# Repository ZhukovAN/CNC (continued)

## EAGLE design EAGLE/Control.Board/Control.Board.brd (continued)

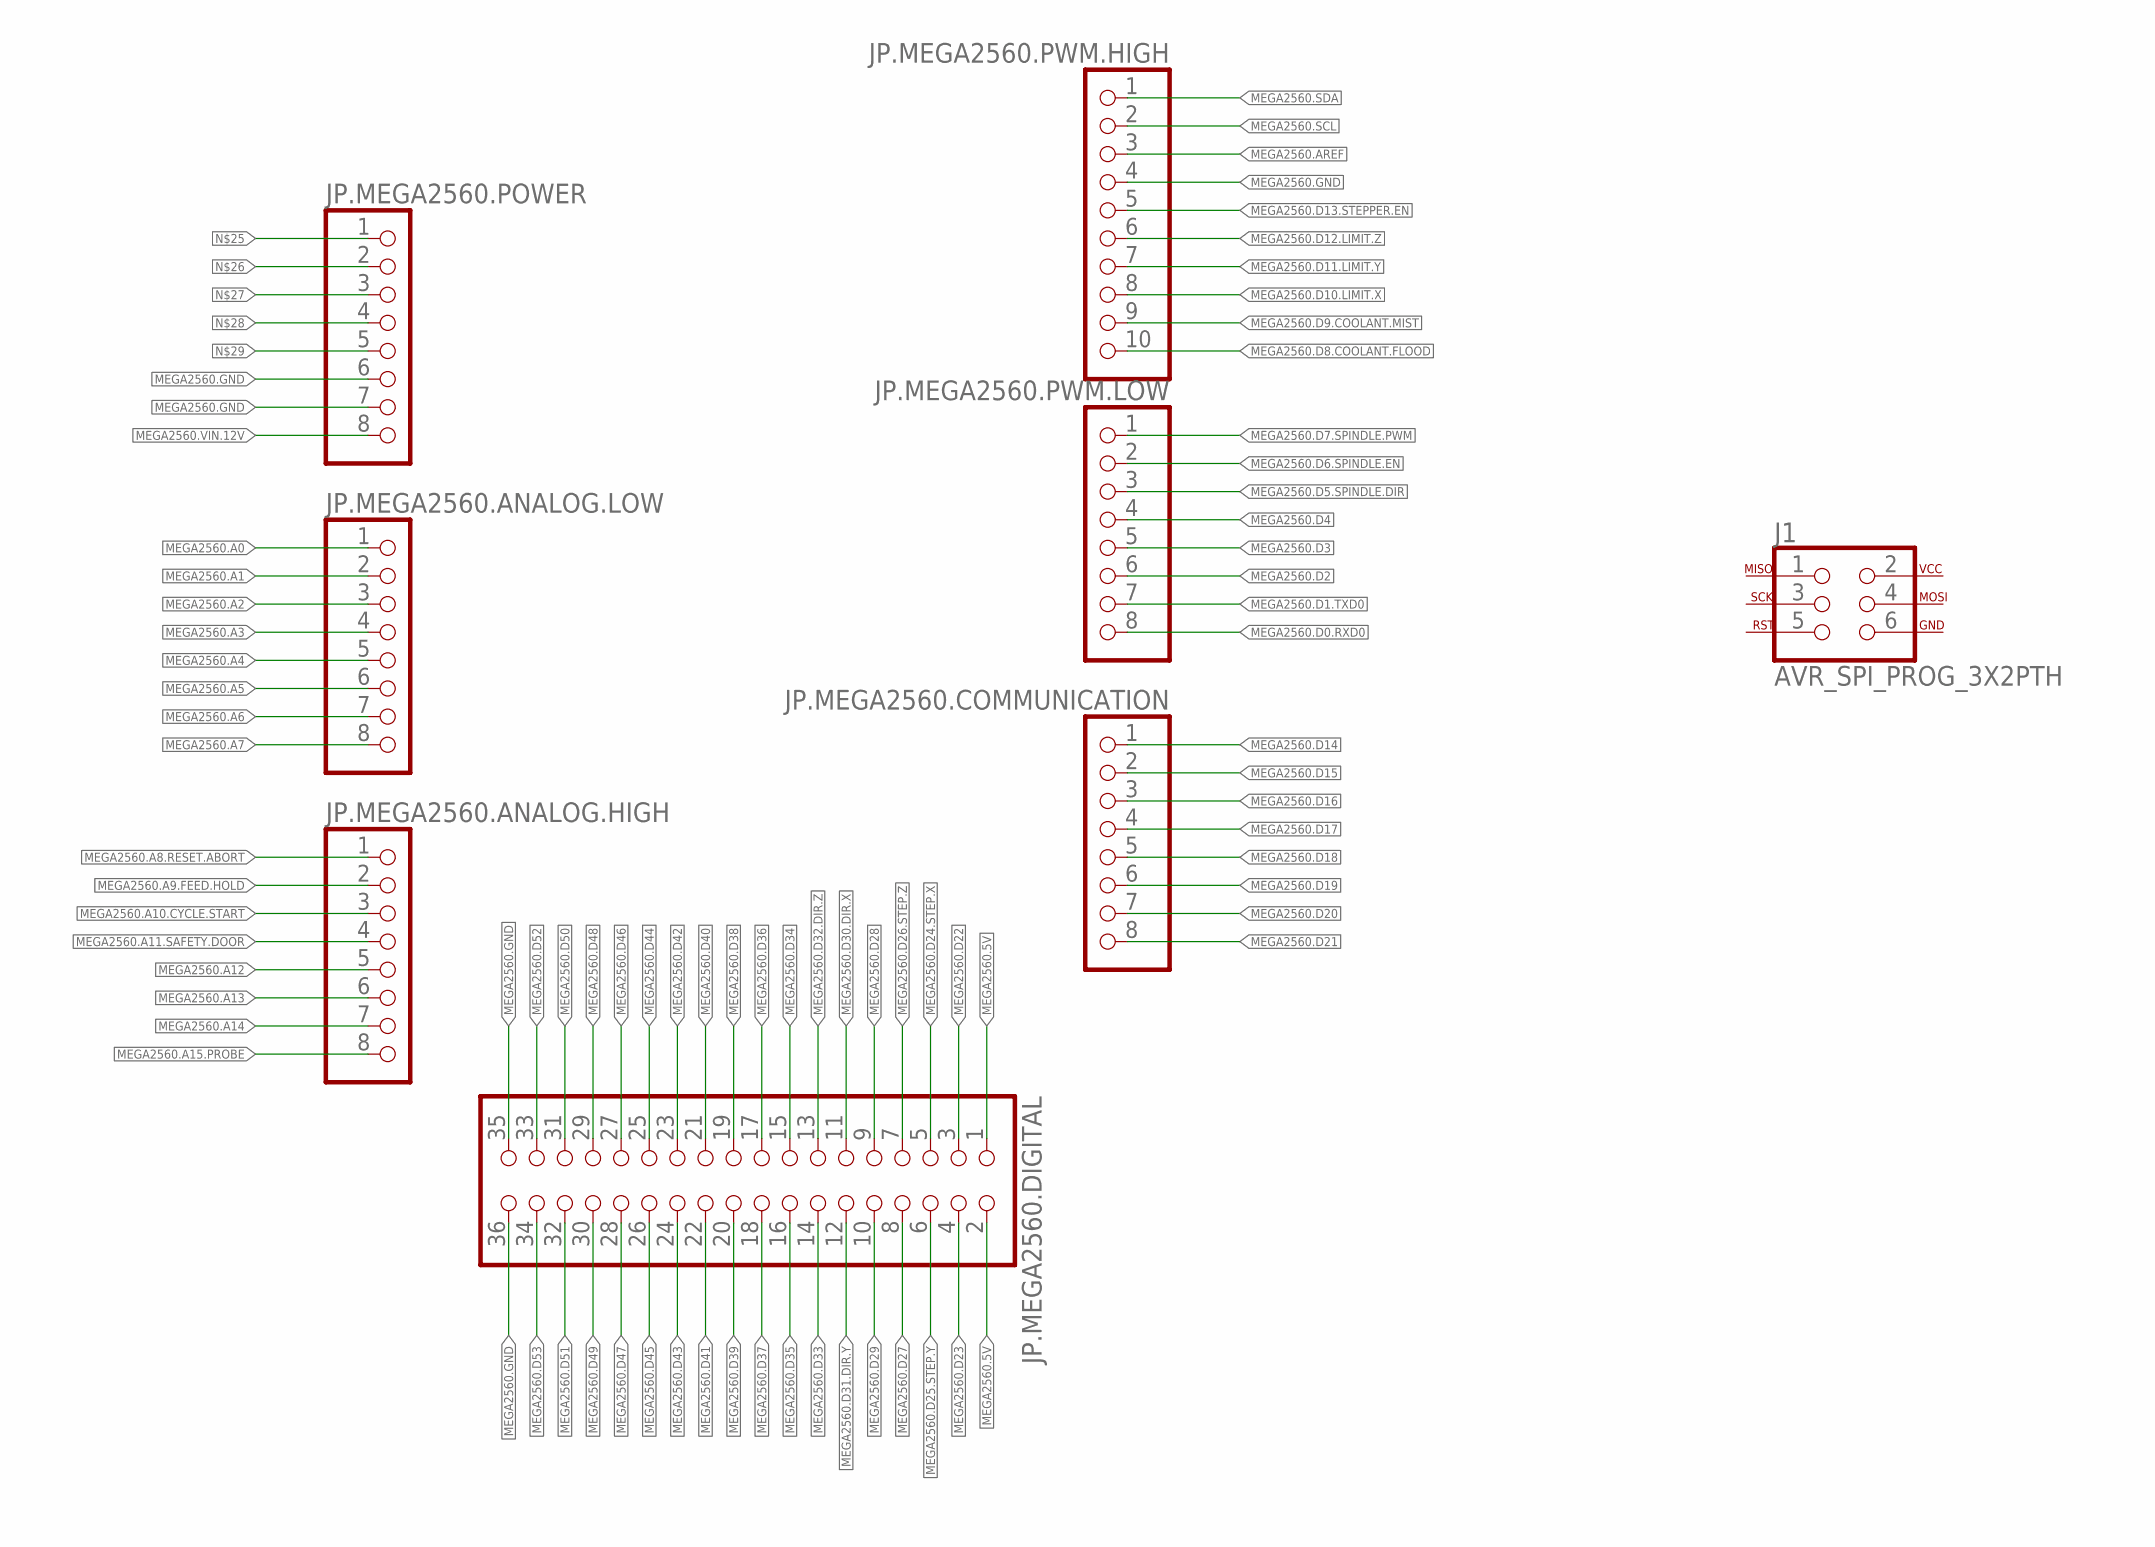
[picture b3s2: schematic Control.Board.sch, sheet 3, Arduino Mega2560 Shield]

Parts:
J1: AVR_SPI_PROG_3X2PTH; 2X3
JP.MEGA2560.ANALOG.HIGH, JP.MEGA2560.ANALOG.LOW, JP.MEGA2560.COMMUNICATION, JP.MEGA2560.POWER, JP.MEGA2560.PWM.LOW: PINHD-1X8; 1X08
JP.MEGA2560.DIGITAL: PINHD-2X18; 2X18
JP.MEGA2560.PWM.HIGH: PINHD-1X10; 1X10

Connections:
MEGA2560.5V: JP.MEGA2560.DIGITAL.1, JP.MEGA2560.DIGITAL.2
MEGA2560.A0: JP.MEGA2560.ANALOG.LOW.1
MEGA2560.A1: JP.MEGA2560.ANALOG.LOW.2
MEGA2560.A2: JP.MEGA2560.ANALOG.LOW.3
MEGA2560.A3: JP.MEGA2560.ANALOG.LOW.4
MEGA2560.A4: JP.MEGA2560.ANALOG.LOW.5
MEGA2560.A5: JP.MEGA2560.ANALOG.LOW.6
MEGA2560.A6: JP.MEGA2560.ANALOG.LOW.7
MEGA2560.A7: JP.MEGA2560.ANALOG.LOW.8
MEGA2560.A8.RESET.ABORT: JP.MEGA2560.ANALOG.HIGH.1; also elsewhere on the board
MEGA2560.A9.FEED.HOLD: JP.MEGA2560.ANALOG.HIGH.2; also elsewhere on the board
MEGA2560.A10.CYCLE.START: JP.MEGA2560.ANALOG.HIGH.3; also elsewhere on the board
MEGA2560.A11.SAFETY.DOOR: JP.MEGA2560.ANALOG.HIGH.4; also elsewhere on the board
MEGA2560.A12: JP.MEGA2560.ANALOG.HIGH.5
MEGA2560.A13: JP.MEGA2560.ANALOG.HIGH.6
MEGA2560.A14: JP.MEGA2560.ANALOG.HIGH.7
MEGA2560.A15.PROBE: JP.MEGA2560.ANALOG.HIGH.8
MEGA2560.AREF: JP.MEGA2560.PWM.HIGH.3
MEGA2560.D0.RXD0: JP.MEGA2560.PWM.LOW.8
MEGA2560.D1.TXD0: JP.MEGA2560.PWM.LOW.7
MEGA2560.D2: JP.MEGA2560.PWM.LOW.6
MEGA2560.D3: JP.MEGA2560.PWM.LOW.5
MEGA2560.D4: JP.MEGA2560.PWM.LOW.4
MEGA2560.D5.SPINDLE.DIR: JP.MEGA2560.PWM.LOW.3
MEGA2560.D6.SPINDLE.EN: JP.MEGA2560.PWM.LOW.2
MEGA2560.D7.SPINDLE.PWM: JP.MEGA2560.PWM.LOW.1
MEGA2560.D8.COOLANT.FLOOD: JP.MEGA2560.PWM.HIGH.10
MEGA2560.D9.COOLANT.MIST: JP.MEGA2560.PWM.HIGH.9
MEGA2560.D10.LIMIT.X: JP.MEGA2560.PWM.HIGH.8; also elsewhere on the board
MEGA2560.D11.LIMIT.Y: JP.MEGA2560.PWM.HIGH.7; also elsewhere on the board
MEGA2560.D12.LIMIT.Z: JP.MEGA2560.PWM.HIGH.6; also elsewhere on the board
MEGA2560.D13.STEPPER.EN: JP.MEGA2560.PWM.HIGH.5; also elsewhere on the board
MEGA2560.D14: JP.MEGA2560.COMMUNICATION.1
MEGA2560.D15: JP.MEGA2560.COMMUNICATION.2
MEGA2560.D16: JP.MEGA2560.COMMUNICATION.3
MEGA2560.D17: JP.MEGA2560.COMMUNICATION.4
MEGA2560.D18: JP.MEGA2560.COMMUNICATION.5
MEGA2560.D19: JP.MEGA2560.COMMUNICATION.6
MEGA2560.D20: JP.MEGA2560.COMMUNICATION.7
MEGA2560.D21: JP.MEGA2560.COMMUNICATION.8
MEGA2560.D22: JP.MEGA2560.DIGITAL.3
MEGA2560.D23: JP.MEGA2560.DIGITAL.4
MEGA2560.D24.STEP.X: JP.MEGA2560.DIGITAL.5; also elsewhere on the board
MEGA2560.D25.STEP.Y: JP.MEGA2560.DIGITAL.6; also elsewhere on the board
MEGA2560.D26.STEP.Z: JP.MEGA2560.DIGITAL.7; also elsewhere on the board
MEGA2560.D27: JP.MEGA2560.DIGITAL.8
MEGA2560.D28: JP.MEGA2560.DIGITAL.9
MEGA2560.D29: JP.MEGA2560.DIGITAL.10
MEGA2560.D30.DIR.X: JP.MEGA2560.DIGITAL.11; also elsewhere on the board
MEGA2560.D31.DIR.Y: JP.MEGA2560.DIGITAL.12; also elsewhere on the board
MEGA2560.D32.DIR.Z: JP.MEGA2560.DIGITAL.13; also elsewhere on the board
MEGA2560.D33: JP.MEGA2560.DIGITAL.14
MEGA2560.D34: JP.MEGA2560.DIGITAL.15
MEGA2560.D35: JP.MEGA2560.DIGITAL.16
MEGA2560.D36: JP.MEGA2560.DIGITAL.17
MEGA2560.D37: JP.MEGA2560.DIGITAL.18
MEGA2560.D38: JP.MEGA2560.DIGITAL.19
MEGA2560.D39: JP.MEGA2560.DIGITAL.20
MEGA2560.D40: JP.MEGA2560.DIGITAL.21
MEGA2560.D41: JP.MEGA2560.DIGITAL.22
MEGA2560.D42: JP.MEGA2560.DIGITAL.23
MEGA2560.D43: JP.MEGA2560.DIGITAL.24
MEGA2560.D44: JP.MEGA2560.DIGITAL.25
MEGA2560.D45: JP.MEGA2560.DIGITAL.26
MEGA2560.D46: JP.MEGA2560.DIGITAL.27
MEGA2560.D47: JP.MEGA2560.DIGITAL.28
MEGA2560.D48: JP.MEGA2560.DIGITAL.29
MEGA2560.D49: JP.MEGA2560.DIGITAL.30
MEGA2560.D50: JP.MEGA2560.DIGITAL.31
MEGA2560.D51: JP.MEGA2560.DIGITAL.32
MEGA2560.D52: JP.MEGA2560.DIGITAL.33
MEGA2560.D53: JP.MEGA2560.DIGITAL.34
MEGA2560.GND: JP.MEGA2560.DIGITAL.35, JP.MEGA2560.DIGITAL.36, JP.MEGA2560.POWER.6, JP.MEGA2560.POWER.7, JP.MEGA2560.PWM.HIGH.4
MEGA2560.SCL: JP.MEGA2560.PWM.HIGH.2
MEGA2560.SDA: JP.MEGA2560.PWM.HIGH.1
MEGA2560.VIN.12V: JP.MEGA2560.POWER.8

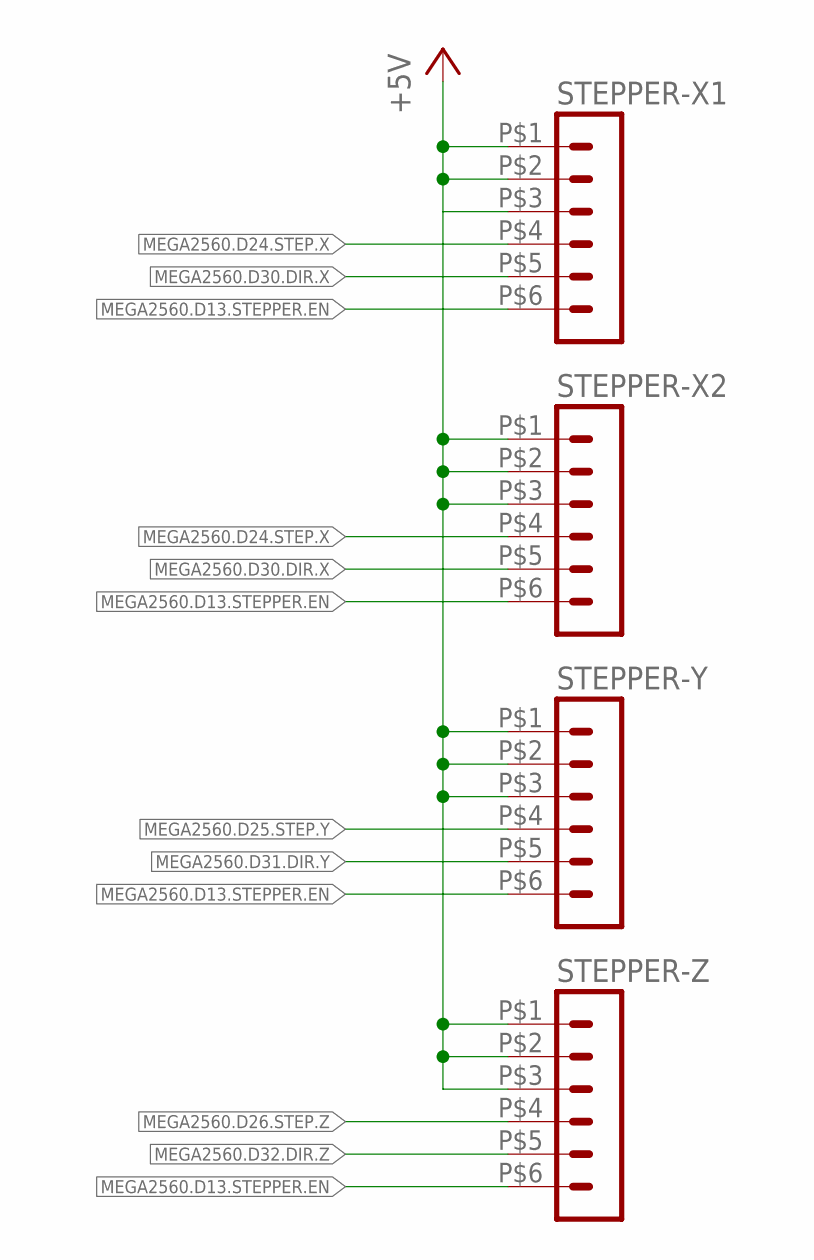
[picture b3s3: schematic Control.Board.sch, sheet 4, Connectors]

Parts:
STEPPER-X1, STEPPER-X2: HEADER_POS6_43045-0600; 43045-0600
STEPPER-Y: HEADER_POS6_43045-0600; 43045-0600
STEPPER-Z: HEADER_POS6_43045-0600; 43045-0600

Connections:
+5V: STEPPER-X1.P$1 (1), STEPPER-X1.P$2 (2), STEPPER-X1.P$3 (3), STEPPER-X2.P$1 (1), STEPPER-X2.P$2 (2), STEPPER-X2.P$3 (3), STEPPER-Y.P$1 (1), STEPPER-Y.P$2 (2), STEPPER-Y.P$3 (3), STEPPER-Z.P$1 (1), STEPPER-Z.P$2 (2), STEPPER-Z.P$3 (3); also elsewhere on the board
MEGA2560.D13.STEPPER.EN: STEPPER-X1.P$6 (6), STEPPER-X2.P$6 (6), STEPPER-Y.P$6 (6), STEPPER-Z.P$6 (6); also elsewhere on the board
MEGA2560.D24.STEP.X: STEPPER-X1.P$4 (4), STEPPER-X2.P$4 (4); also elsewhere on the board
MEGA2560.D25.STEP.Y: STEPPER-Y.P$4 (4); also elsewhere on the board
MEGA2560.D26.STEP.Z: STEPPER-Z.P$4 (4); also elsewhere on the board
MEGA2560.D30.DIR.X: STEPPER-X1.P$5 (5), STEPPER-X2.P$5 (5); also elsewhere on the board
MEGA2560.D31.DIR.Y: STEPPER-Y.P$5 (5); also elsewhere on the board
MEGA2560.D32.DIR.Z: STEPPER-Z.P$5 (5); also elsewhere on the board

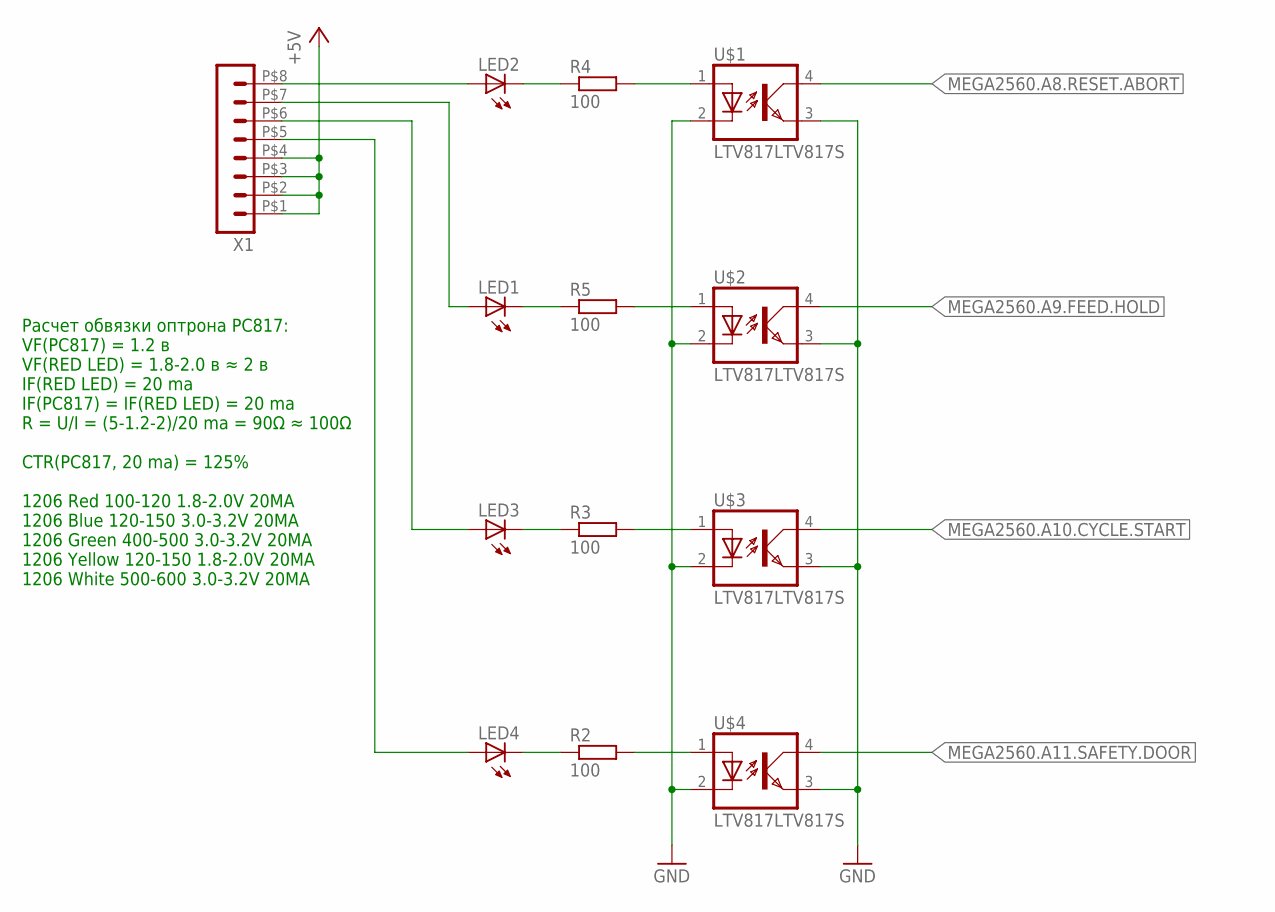
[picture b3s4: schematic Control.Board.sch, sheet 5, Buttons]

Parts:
LED1, LED2, LED3, LED4: LEDCHIPLED_1206; CHIPLED_1206
R2, R3, R4, R5: 100; M1206
U$1, U$2, U$3, U$4: LTV817LTV817S; DIL4-SMD
X1: HEADER_POS8_43045-0800; 43045-0800

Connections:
+5V: X1.P$1 (1), X1.P$2 (2), X1.P$3 (3), X1.P$4 (4); also elsewhere on the board
GND: U$1.2 (C), U$1.3 (EMIT), U$2.2 (C), U$2.3 (EMIT), U$3.2 (C), U$3.3 (EMIT), U$4.2 (C), U$4.3 (EMIT); also elsewhere on the board
MEGA2560.A8.RESET.ABORT: U$1.4 (COL); also elsewhere on the board
MEGA2560.A9.FEED.HOLD: U$2.4 (COL); also elsewhere on the board
MEGA2560.A10.CYCLE.START: U$3.4 (COL); also elsewhere on the board
MEGA2560.A11.SAFETY.DOOR: U$4.4 (COL); also elsewhere on the board
unnamed: LED2.A, X1.P$8 (8)
unnamed: LED1.A, X1.P$7 (7)
unnamed: LED3.A, X1.P$6 (6)
unnamed: LED2.C, R4.1
unnamed: R4.2, U$1.1 (A)
unnamed: R5.2, U$2.1 (A)
unnamed: LED1.C, R5.1
unnamed: LED4.A, X1.P$5 (5)
unnamed: LED3.C, R3.1
unnamed: LED4.C, R2.1
unnamed: R2.2, U$4.1 (A)
unnamed: R3.2, U$3.1 (A)

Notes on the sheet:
Расчет обвязки оптрона PC817: VF(PC817) = 1.2 в VF(RED LED) = 1.8-2.0 в ≈ 2 в IF(RED LED) = 20 ma IF(PC817) = IF(RED LED) = 20 ma R = U/I = (5-1.2-2)/20 ma = 90Ω ≈ 100Ω CTR(PC817, 20 ma) = 125% 1206 Red 100-120 1.8-2.0V 20MA 1206 Blue 120-150 3.0-3.2V 20MA 1206 Green 400-500 3.0-3.2V 20MA 1206 Yell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

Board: 2 copper layers, 50 parts (0 on the bottom side), 49 nets, no tracks yet.

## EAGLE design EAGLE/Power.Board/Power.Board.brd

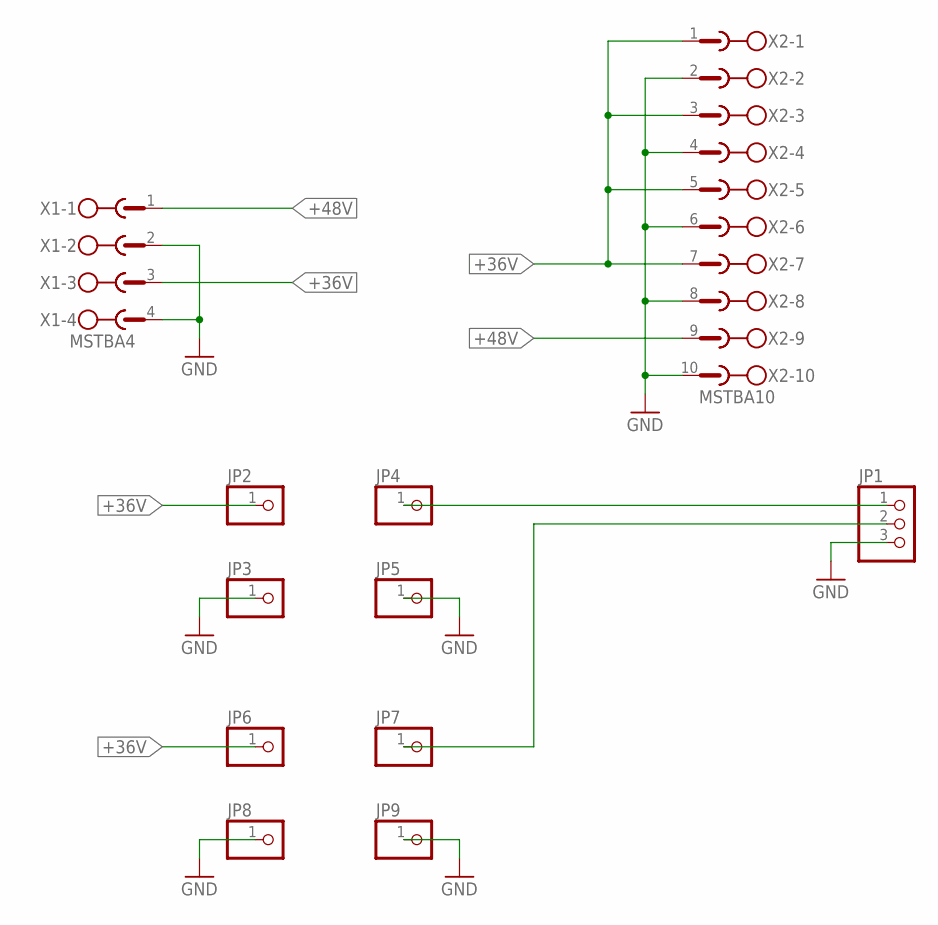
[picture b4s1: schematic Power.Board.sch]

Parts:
JP1: PINHD-1X3/90; 1X03/90
JP2, JP3, JP4, JP5, JP6, JP7, JP8, JP9: PINHD-1X1; 1X01
X1: MSTBA4
X2: MSTBA10

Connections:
+36V: JP2.1, JP6.1, X1.3, X2.1, X2.3, X2.5, X2.7
+48V: X1.1, X2.9
GND: JP1.3, JP3.1, JP5.1, JP8.1, JP9.1, X1.2, X1.4, X2.2, X2.4, X2.6, X2.8, X2.10
unnamed: JP1.1, JP4.1
unnamed: JP1.2, JP7.1

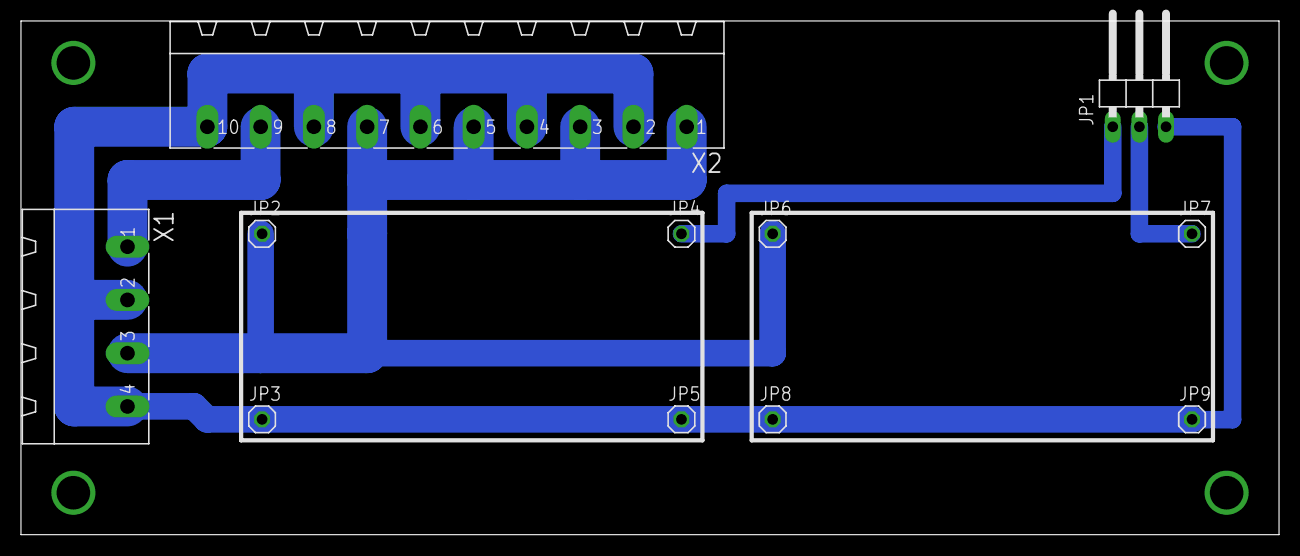
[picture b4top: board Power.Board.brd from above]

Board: 2 copper layers, 120.0 x 49.0 mm, 11 parts (0 on the bottom side), 5 nets.

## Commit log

2018-04-15 EagleCAD files added
2018-04-16 Phoenix connectors library added
2018-04-16 20180416
2018-04-17 CNC.mmap added
2018-04-19 Molex Micro-Fit library added
2018-04-23 20180423
2018-04-24 20180424
2018-04-26 PCB-GCODE-3.6.0.4 added
2018-04-27 20180427
2018-05-03 Net173.LBR added
2018-05-03 20180503
2018-05-04 Folder structure changed
2018-05-04 20180504
2018-05-05 20180505
2018-05-10 20180510
2018-05-11 20180511
2018-05-13 20180513
2018-05-19 20180519
2018-05-19 Auto stash before merge of "master" and "origin/master"
2018-05-20 20180520
2018-05-21 20180521
2018-05-26 20180526
2018-05-29 20180529
2018-05-30 20180530
2018-05-31 20180531
